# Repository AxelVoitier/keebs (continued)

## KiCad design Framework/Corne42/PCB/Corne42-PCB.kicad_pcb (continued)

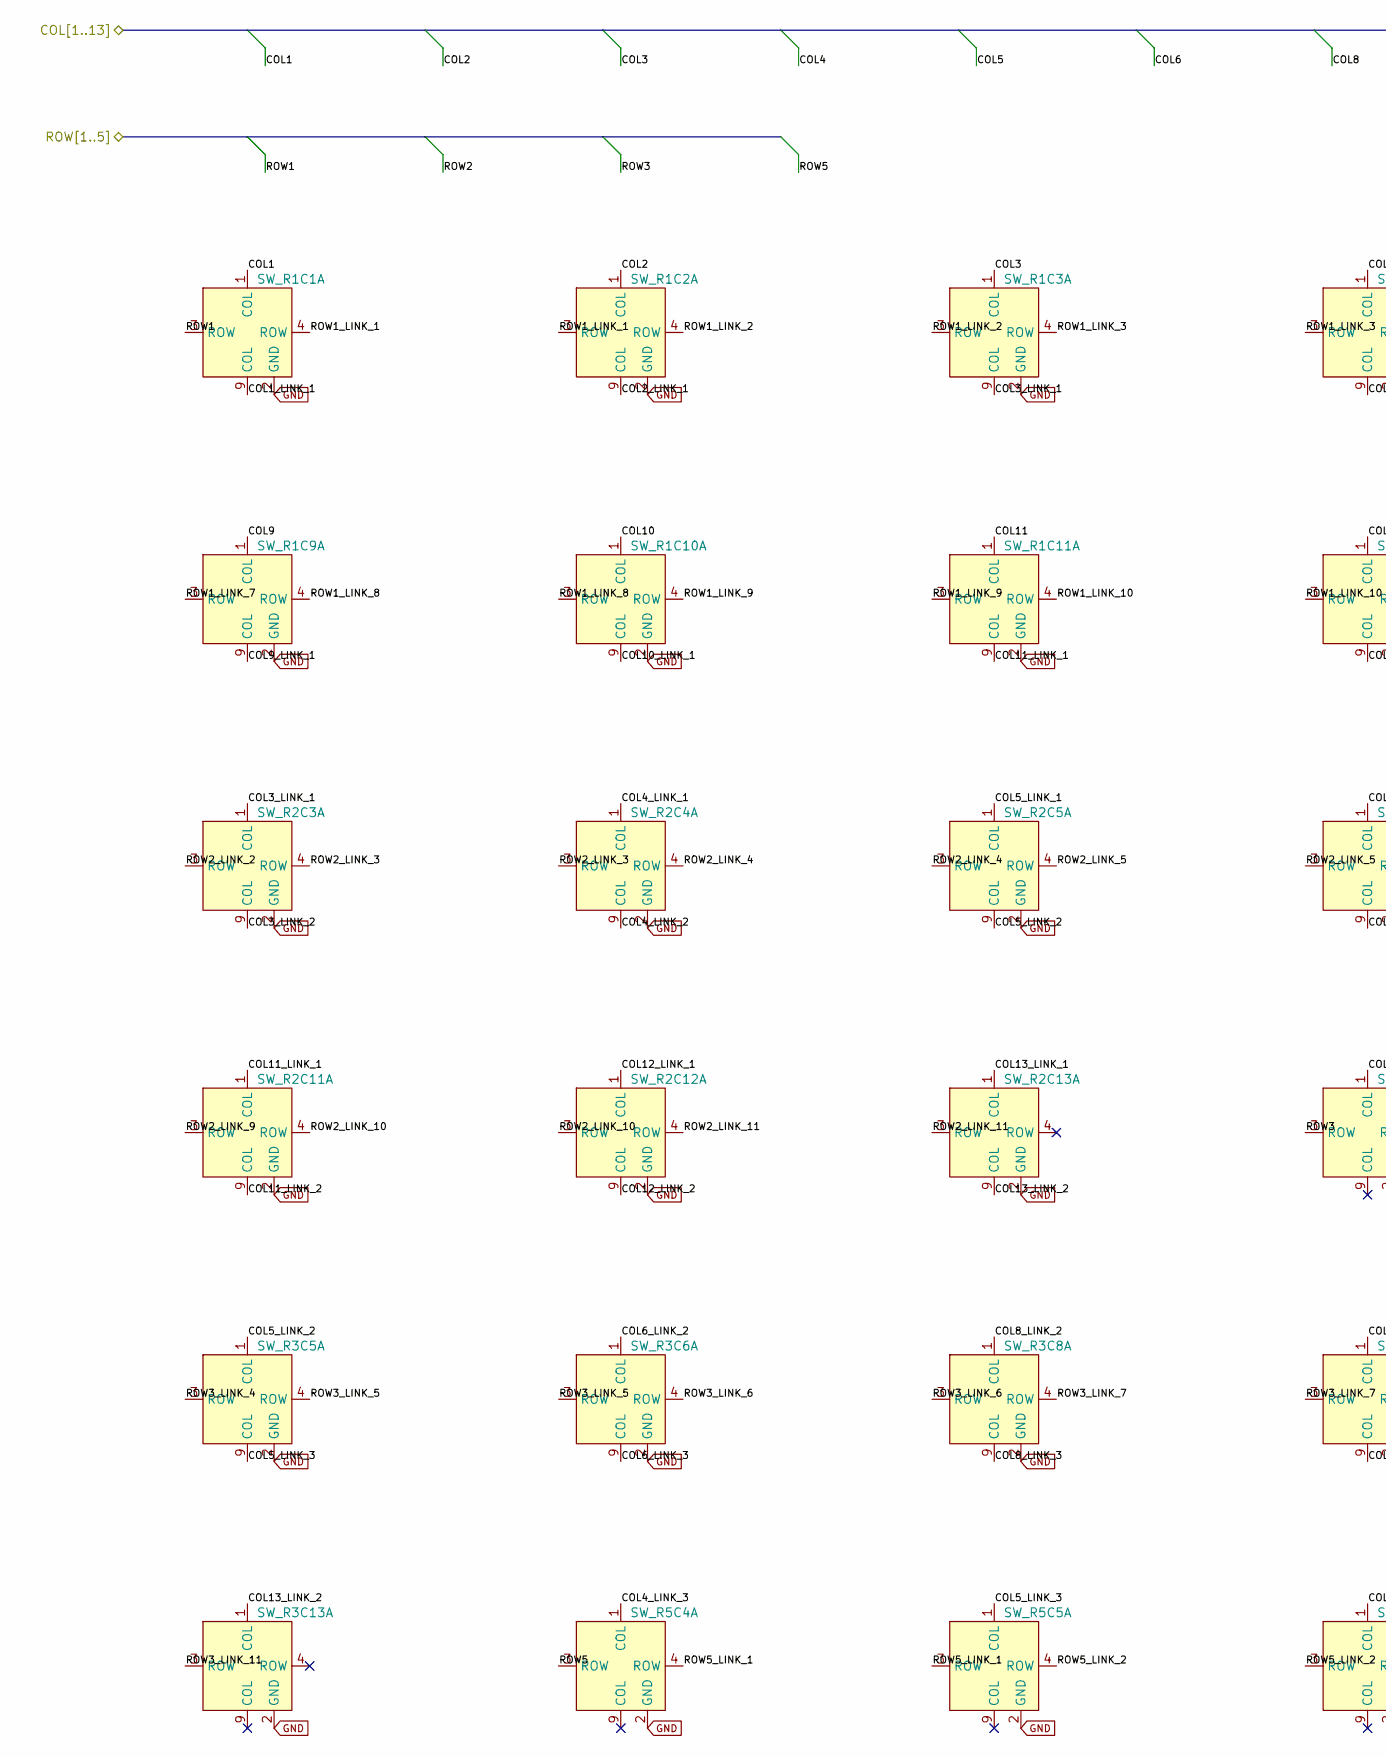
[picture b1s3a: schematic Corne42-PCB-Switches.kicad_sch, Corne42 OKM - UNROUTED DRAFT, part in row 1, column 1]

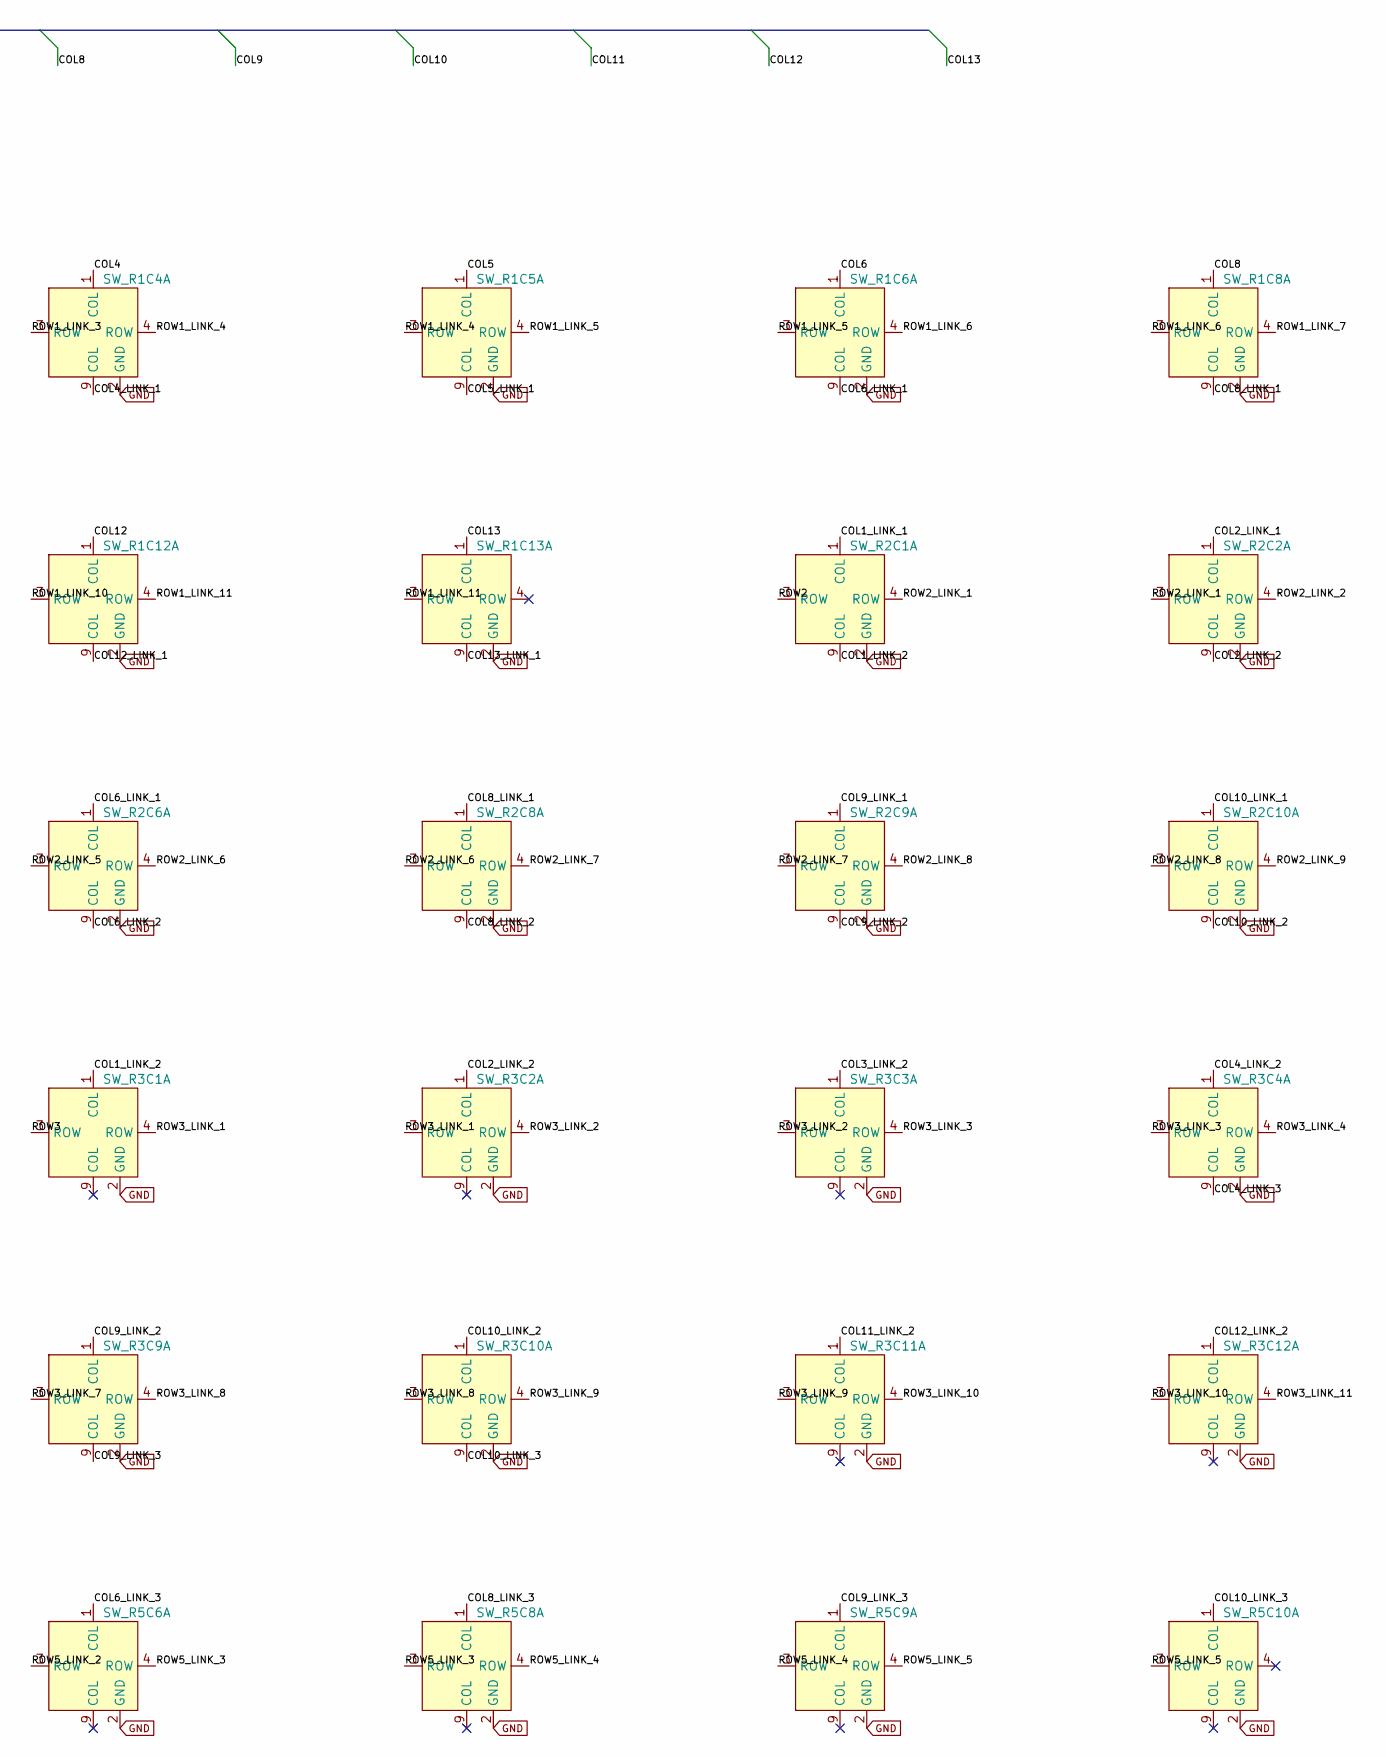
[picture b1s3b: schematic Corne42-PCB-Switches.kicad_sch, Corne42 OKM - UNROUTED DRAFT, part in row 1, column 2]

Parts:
SW_R1C1: One Key Module_Corne42_SW_R1C1
SW_R1C2: One Key Module_Corne42_SW_R1C2
SW_R1C3: One Key Module_Corne42_SW_R1C3
SW_R1C4: One Key Module_Corne42_SW_R1C4
SW_R1C5: One Key Module_Corne42_SW_R1C5
SW_R1C6: One Key Module_Corne42_SW_R1C6
SW_R1C8: One Key Module_Corne42_SW_R1C8
SW_R1C9: One Key Module_Corne42_SW_R1C9
SW_R1C10: One Key Module_Corne42_SW_R1C10
SW_R1C11: One Key Module_Corne42_SW_R1C11
SW_R1C12: One Key Module_Corne42_SW_R1C12
SW_R1C13: One Key Module_Corne42_SW_R1C13
SW_R2C1: One Key Module_Corne42_SW_R2C1
SW_R2C2: One Key Module_Corne42_SW_R2C2
SW_R2C3: One Key Module_Corne42_SW_R2C3
SW_R2C4: One Key Module_Corne42_SW_R2C4
SW_R2C5: One Key Module_Corne42_SW_R2C5
SW_R2C6: One Key Module_Corne42_SW_R2C6
SW_R2C8: One Key Module_Corne42_SW_R2C8
SW_R2C9: One Key Module_Corne42_SW_R2C9
SW_R2C10: One Key Module_Corne42_SW_R2C10
SW_R2C11: One Key Module_Corne42_SW_R2C11
SW_R2C12: One Key Module_Corne42_SW_R2C12
SW_R2C13: One Key Module_Corne42_SW_R2C13
SW_R3C1: One Key Module_Corne42_SW_R3C1
SW_R3C2: One Key Module_Corne42_SW_R3C2
SW_R3C3: One Key Module_Corne42_SW_R3C3
SW_R3C4: One Key Module_Corne42_SW_R3C4
SW_R3C5: One Key Module_Corne42_SW_R3C5
SW_R3C6: One Key Module_Corne42_SW_R3C6
SW_R3C8: One Key Module_Corne42_SW_R3C8
SW_R3C9: One Key Module_Corne42_SW_R3C9
SW_R3C10: One Key Module_Corne42_SW_R3C10
SW_R3C11: One Key Module_Corne42_SW_R3C11
SW_R3C12: One Key Module_Corne42_SW_R3C12
SW_R3C13: One Key Module_Corne42_SW_R3C13
SW_R5C4: One Key Module_Corne42_SW_R5C4
SW_R5C5: One Key Module_Corne42_SW_R5C5
SW_R5C6: One Key Module_Corne42_SW_R5C6
SW_R5C8: One Key Module_Corne42_SW_R5C8
SW_R5C9: One Key Module_Corne42_SW_R5C9
SW_R5C10: One Key Module_Corne42_SW_R5C10

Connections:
/COL1: SW_R1C1.1 (COL); also elsewhere on the board
/COL2: SW_R1C2.1 (COL); also elsewhere on the board
/COL3: SW_R1C3.1 (COL); also elsewhere on the board
/COL4: SW_R1C4.1 (COL); also elsewhere on the board
/COL5: SW_R1C5.1 (COL); also elsewhere on the board
/COL6: SW_R1C6.1 (COL); also elsewhere on the board
/COL8: SW_R1C8.1 (COL); also elsewhere on the board
/COL9: SW_R1C9.1 (COL); also elsewhere on the board
/COL10: SW_R1C10.1 (COL); also elsewhere on the board
/COL11: SW_R1C11.1 (COL); also elsewhere on the board
/COL12: SW_R1C12.1 (COL); also elsewhere on the board
/COL13: SW_R1C13.1 (COL); also elsewhere on the board
/ROW1: SW_R1C1.3 (ROW); also elsewhere on the board
/ROW2: SW_R2C1.3 (ROW); also elsewhere on the board
/ROW3: SW_R3C1.3 (ROW); also elsewhere on the board
/ROW5: SW_R5C4.3 (ROW); also elsewhere on the board
/Switches/COL1_LINK_1: SW_R1C1.9 (COL), SW_R2C1.1 (COL)
/Switches/COL1_LINK_2: SW_R2C1.9 (COL), SW_R3C1.1 (COL)
/Switches/COL2_LINK_1: SW_R1C2.9 (COL), SW_R2C2.1 (COL)
/Switches/COL2_LINK_2: SW_R2C2.9 (COL), SW_R3C2.1 (COL)
/Switches/COL3_LINK_1: SW_R1C3.9 (COL), SW_R2C3.1 (COL)
/Switches/COL3_LINK_2: SW_R2C3.9 (COL), SW_R3C3.1 (COL)
/Switches/COL4_LINK_1: SW_R1C4.9 (COL), SW_R2C4.1 (COL)
/Switches/COL4_LINK_2: SW_R2C4.9 (COL), SW_R3C4.1 (COL)
/Switches/COL4_LINK_3: SW_R3C4.9 (COL), SW_R5C4.1 (COL)
/Switches/COL5_LINK_1: SW_R1C5.9 (COL), SW_R2C5.1 (COL)
/Switches/COL5_LINK_2: SW_R2C5.9 (COL), SW_R3C5.1 (COL)
/Switches/COL5_LINK_3: SW_R3C5.9 (COL), SW_R5C5.1 (COL)
/Switches/COL6_LINK_1: SW_R1C6.9 (COL), SW_R2C6.1 (COL)
/Switches/COL6_LINK_2: SW_R2C6.9 (COL), SW_R3C6.1 (COL)
/Switches/COL6_LINK_3: SW_R3C6.9 (COL), SW_R5C6.1 (COL)
/Switches/COL8_LINK_1: SW_R1C8.9 (COL), SW_R2C8.1 (COL)
/Switches/COL8_LINK_2: SW_R2C8.9 (COL), SW_R3C8.1 (COL)
/Switches/COL8_LINK_3: SW_R3C8.9 (COL), SW_R5C8.1 (COL)
/Switches/COL9_LINK_1: SW_R1C9.9 (COL), SW_R2C9.1 (COL)
/Switches/COL9_LINK_2: SW_R2C9.9 (COL), SW_R3C9.1 (COL)
/Switches/COL9_LINK_3: SW_R3C9.9 (COL), SW_R5C9.1 (COL)
/Switches/COL10_LINK_1: SW_R1C10.9 (COL), SW_R2C10.1 (COL)
/Switches/COL10_LINK_2: SW_R2C10.9 (COL), SW_R3C10.1 (COL)
/Switches/COL10_LINK_3: SW_R3C10.9 (COL), SW_R5C10.1 (COL)
/Switches/COL11_LINK_1: SW_R1C11.9 (COL), SW_R2C11.1 (COL)
/Switches/COL11_LINK_2: SW_R2C11.9 (COL), SW_R3C11.1 (COL)
/Switches/COL12_LINK_1: SW_R1C12.9 (COL), SW_R2C12.1 (COL)
/Switches/COL12_LINK_2: SW_R2C12.9 (COL), SW_R3C12.1 (COL)
/Switches/COL13_LINK_1: SW_R1C13.9 (COL), SW_R2C13.1 (COL)
/Switches/COL13_LINK_2: SW_R2C13.9 (COL), SW_R3C13.1 (COL)
/Switches/ROW1_LINK_1: SW_R1C1.4 (ROW), SW_R1C2.3 (ROW)
/Switches/ROW1_LINK_2: SW_R1C2.4 (ROW), SW_R1C3.3 (ROW)
/Switches/ROW1_LINK_3: SW_R1C3.4 (ROW), SW_R1C4.3 (ROW)
/Switches/ROW1_LINK_4: SW_R1C4.4 (ROW), SW_R1C5.3 (ROW)
/Switches/ROW1_LINK_5: SW_R1C5.4 (ROW), SW_R1C6.3 (ROW)
/Switches/ROW1_LINK_6: SW_R1C6.4 (ROW), SW_R1C8.3 (ROW)
/Switches/ROW1_LINK_7: SW_R1C8.4 (ROW), SW_R1C9.3 (ROW)
/Switches/ROW1_LINK_8: SW_R1C9.4 (ROW), SW_R1C10.3 (ROW)
/Switches/ROW1_LINK_9: SW_R1C10.4 (ROW), SW_R1C11.3 (ROW)
/Switches/ROW1_LINK_10: SW_R1C11.4 (ROW), SW_R1C12.3 (ROW)
/Switches/ROW1_LINK_11: SW_R1C12.4 (ROW), SW_R1C13.3 (ROW)
/Switches/ROW2_LINK_1: SW_R2C1.4 (ROW), SW_R2C2.3 (ROW)
/Switches/ROW2_LINK_2: SW_R2C2.4 (ROW), SW_R2C3.3 (ROW)
/Switches/ROW2_LINK_3: SW_R2C3.4 (ROW), SW_R2C4.3 (ROW)
/Switches/ROW2_LINK_4: SW_R2C4.4 (ROW), SW_R2C5.3 (ROW)
/Switches/ROW2_LINK_5: SW_R2C5.4 (ROW), SW_R2C6.3 (ROW)
/Switches/ROW2_LINK_6: SW_R2C6.4 (ROW), SW_R2C8.3 (ROW)
/Switches/ROW2_LINK_7: SW_R2C8.4 (ROW), SW_R2C9.3 (ROW)
/Switches/ROW2_LINK_8: SW_R2C9.4 (ROW), SW_R2C10.3 (ROW)
/Switches/ROW2_LINK_9: SW_R2C10.4 (ROW), SW_R2C11.3 (ROW)
/Switches/ROW2_LINK_10: SW_R2C11.4 (ROW), SW_R2C12.3 (ROW)
/Switches/ROW2_LINK_11: SW_R2C12.4 (ROW), SW_R2C13.3 (ROW)
/Switches/ROW3_LINK_1: SW_R3C1.4 (ROW), SW_R3C2.3 (ROW)
/Switches/ROW3_LINK_2: SW_R3C2.4 (ROW), SW_R3C3.3 (ROW)
/Switches/ROW3_LINK_3: SW_R3C3.4 (ROW), SW_R3C4.3 (ROW)
/Switches/ROW3_LINK_4: SW_R3C4.4 (ROW), SW_R3C5.3 (ROW)
/Switches/ROW3_LINK_5: SW_R3C5.4 (ROW), SW_R3C6.3 (ROW)
/Switches/ROW3_LINK_6: SW_R3C6.4 (ROW), SW_R3C8.3 (ROW)
/Switches/ROW3_LINK_7: SW_R3C8.4 (ROW), SW_R3C9.3 (ROW)
/Switches/ROW3_LINK_8: SW_R3C9.4 (ROW), SW_R3C10.3 (ROW)
/Switches/ROW3_LINK_9: SW_R3C10.4 (ROW), SW_R3C11.3 (ROW)
/Switches/ROW3_LINK_10: SW_R3C11.4 (ROW), SW_R3C12.3 (ROW)
/Switches/ROW3_LINK_11: SW_R3C12.4 (ROW), SW_R3C13.3 (ROW)
/Switches/ROW5_LINK_1: SW_R5C4.4 (ROW), SW_R5C5.3 (ROW)
/Switches/ROW5_LINK_2: SW_R5C5.4 (ROW), SW_R5C6.3 (ROW)
/Switches/ROW5_LINK_3: SW_R5C6.4 (ROW), SW_R5C8.3 (ROW)
/Switches/ROW5_LINK_4: SW_R5C8.4 (ROW), SW_R5C9.3 (ROW)
/Switches/ROW5_LINK_5: SW_R5C9.4 (ROW), SW_R5C10.3 (ROW)
GND: SW_R1C1.2 (GND), SW_R1C1.10 (GND), SW_R1C2.2 (GND), SW_R1C2.10 (GND), SW_R1C3.2 (GND), SW_R1C3.10 (GND), SW_R1C4.2 (GND), SW_R1C4.10 (GND), SW_R1C5.2 (GND), SW_R1C5.10 (GND), SW_R1C6.2 (GND), SW_R1C6.10 (GND), SW_R1C8.2 (GND), SW_R1C8.10 (GND), SW_R1C9.2 (GND), SW_R1C9.10 (GND), SW_R1C10.2 (GND), SW_R1C10.10 (GND), SW_R1C11.2 (GND), SW_R1C11.10 (GND), SW_R1C12.2 (GND), SW_R1C12.10 (GND), SW_R1C13.2 (GND), SW_R1C13.10 (GND), SW_R2C1.2 (GND), SW_R2C1.10 (GND), SW_R2C2.2 (GND), SW_R2C2.10 (GND), SW_R2C3.2 (GND), SW_R2C3.10 (GND), SW_R2C4.2 (GND), SW_R2C4.10 (GND), SW_R2C5.2 (GND), SW_R2C5.10 (GND), SW_R2C6.2 (GND), SW_R2C6.10 (GND), SW_R2C8.2 (GND), SW_R2C8.10 (GND), SW_R2C9.2 (GND), SW_R2C9.10 (GND), SW_R2C10.2 (GND), SW_R2C10.10 (GND), SW_R2C11.2 (GND), SW_R2C11.10 (GND), SW_R2C12.2 (GND), SW_R2C12.10 (GND), SW_R2C13.2 (GND), SW_R2C13.10 (GND), SW_R3C1.2 (GND), SW_R3C1.10 (GND), SW_R3C2.2 (GND), SW_R3C2.10 (GND), SW_R3C3.2 (GND), SW_R3C3.10 (GND), SW_R3C4.2 (GND), SW_R3C4.10 (GND), SW_R3C5.2 (GND), SW_R3C5.10 (GND), SW_R3C6.2 (GND), SW_R3C6.10 (GND), SW_R3C8.2 (GND), SW_R3C8.10 (GND), SW_R3C9.2 (GND), SW_R3C9.10 (GND), SW_R3C10.2 (GND), SW_R3C10.10 (GND), SW_R3C11.2 (GND), SW_R3C11.10 (GND), SW_R3C12.2 (GND), SW_R3C12.10 (GND), SW_R3C13.2 (GND), SW_R3C13.10 (GND), SW_R5C4.2 (GND), SW_R5C4.10 (GND), SW_R5C5.2 (GND), SW_R5C5.10 (GND), SW_R5C6.2 (GND), SW_R5C6.10 (GND), SW_R5C8.2 (GND), SW_R5C8.10 (GND), SW_R5C9.2 (GND), SW_R5C9.10 (GND), SW_R5C10.2 (GND), SW_R5C10.10 (GND); also elsewhere on the board

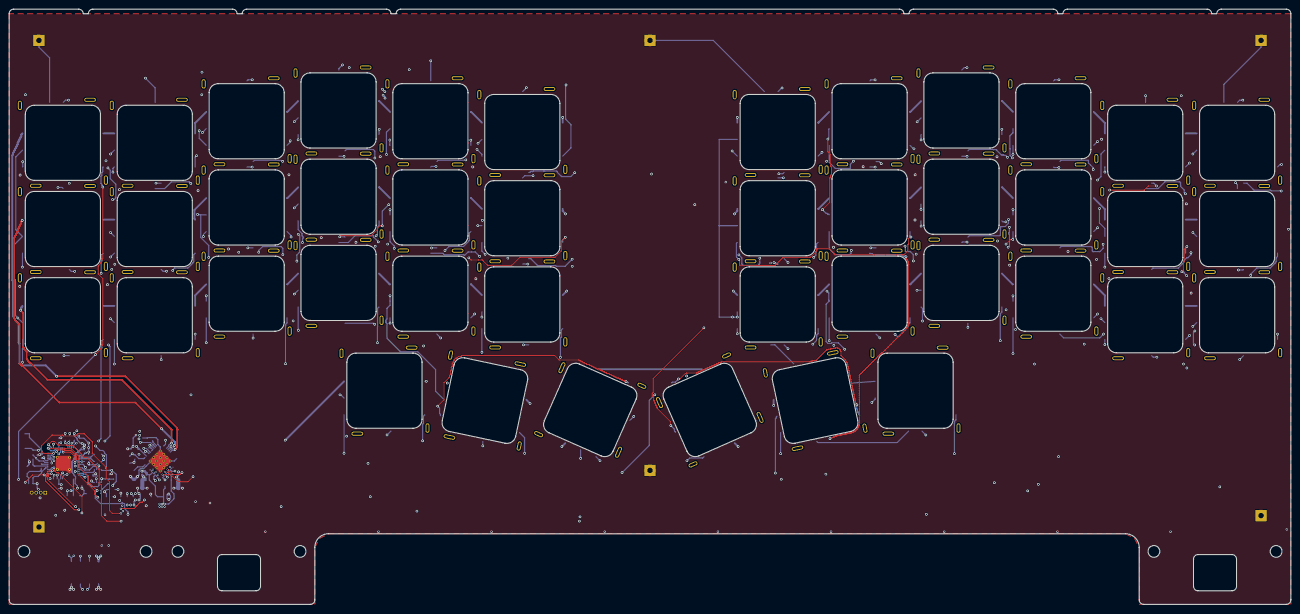
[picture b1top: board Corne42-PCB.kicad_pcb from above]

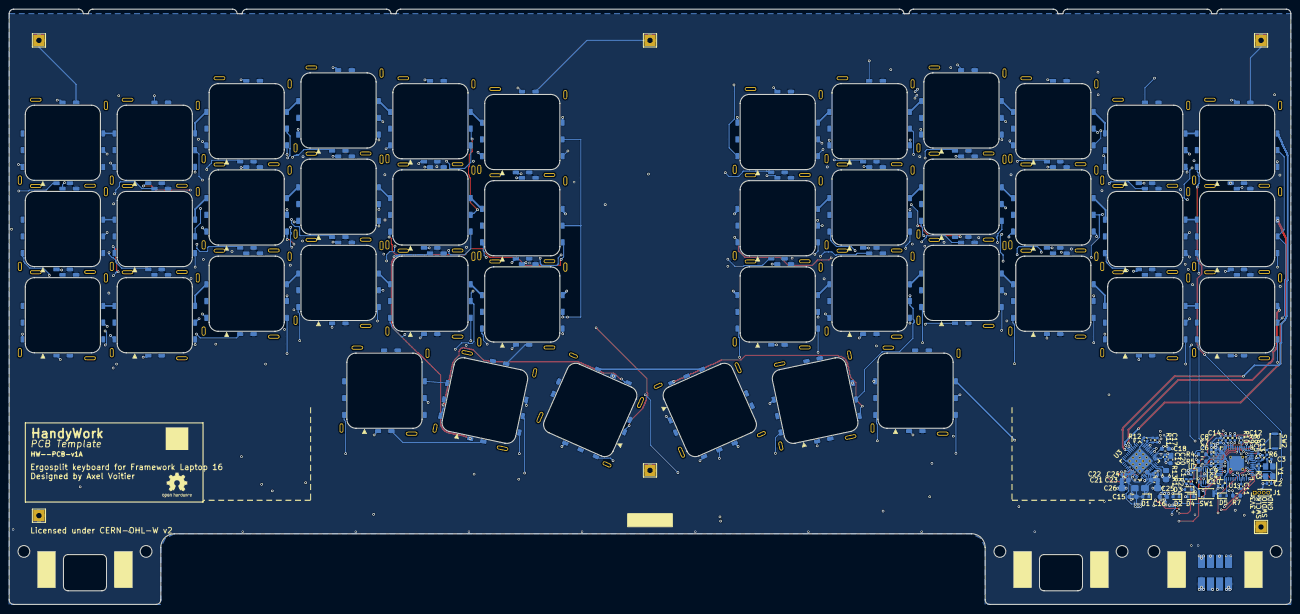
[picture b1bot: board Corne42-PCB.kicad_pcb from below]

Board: 4 copper layers, 283.2 x 131.5 mm, 100 parts (57 on the bottom side), 167 nets.

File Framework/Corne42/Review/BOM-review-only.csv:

"Comment","Designator","Footprint","LCSC Part Number"
"100n","C1,C4,C5,C8,C9,C10,C11,C12,C13,C14,C17,C19,C22,C24","Capacitor_SMD:C_0402_1005Metric","C1525"
"15p","C2,C3","Capacitor_SMD:C_0402_1005Metric","C1548"
"1u","C6,C7","Capacitor_SMD:C_0402_1005Metric","C52923"
"10u","C15,C16","Capacitor_SMD:C_0603_1608Metric","C19702"
"470n","C18,C20,C21,C23","Capacitor_SMD:C_0603_1608Metric","C1623"
"10u","C25,C26","Capacitor_Tantalum_SMD:CP_EIA-3216-18_Kemet-A_HandSolder","C7171"
"TVS","D1,D2,D3,D4,D5","Diode_SMD:D_SOD-523","C20615820"
"1k","R2,R3","Resistor_SMD:R_0402_1005Metric","C11702"
"27.4","R4,R5","Resistor_SMD:R_0603_1608Metric","C25190"
"330k","R7","Resistor_SMD:R_0603_1608Metric","C23137"
"2k","R8,R9","Resistor_SMD:R_0402_1005Metric","C4109"
"100k","R10,R11,R12","Resistor_SMD:R_0402_1005Metric","C25741"
"22k","R13","Resistor_SMD:R_0805_2012Metric_Pad1.20x1.40mm_HandSolder","C17560"
"KXT3","SW1,SW2","Button_Switch_SMD:SW_SPST_CK_KXT3","C221822"
"RP2040","U1","Package_DFN_QFN:QFN-56-1EP_7x7mm_P0.4mm_EP3.2x3.2mm_ThermalVias","C2040"
"W25Q16JV","U2","Package_SON:Winbond_USON-8-1EP_3x2mm_P0.5mm_EP0.2x1.6mm","C2843335"
"IS31FL3733B-QF","U3","Package_DFN_QFN:QFN-48-1EP_6x6mm_P0.4mm_EP4.2x4.2mm_ThermalVias","C5362338"
"12.000 MHz","Y1","Crystal:Crystal_SMD_Abracon_ABM8AIG-4Pin_3.2x2.5mm","C20625731"

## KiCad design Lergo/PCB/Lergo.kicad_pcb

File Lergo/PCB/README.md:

# Lergo modular PCB

## Schematic
[Schematic PDF](Doc/Lergo-schematic.pdf)

## PCB Layout

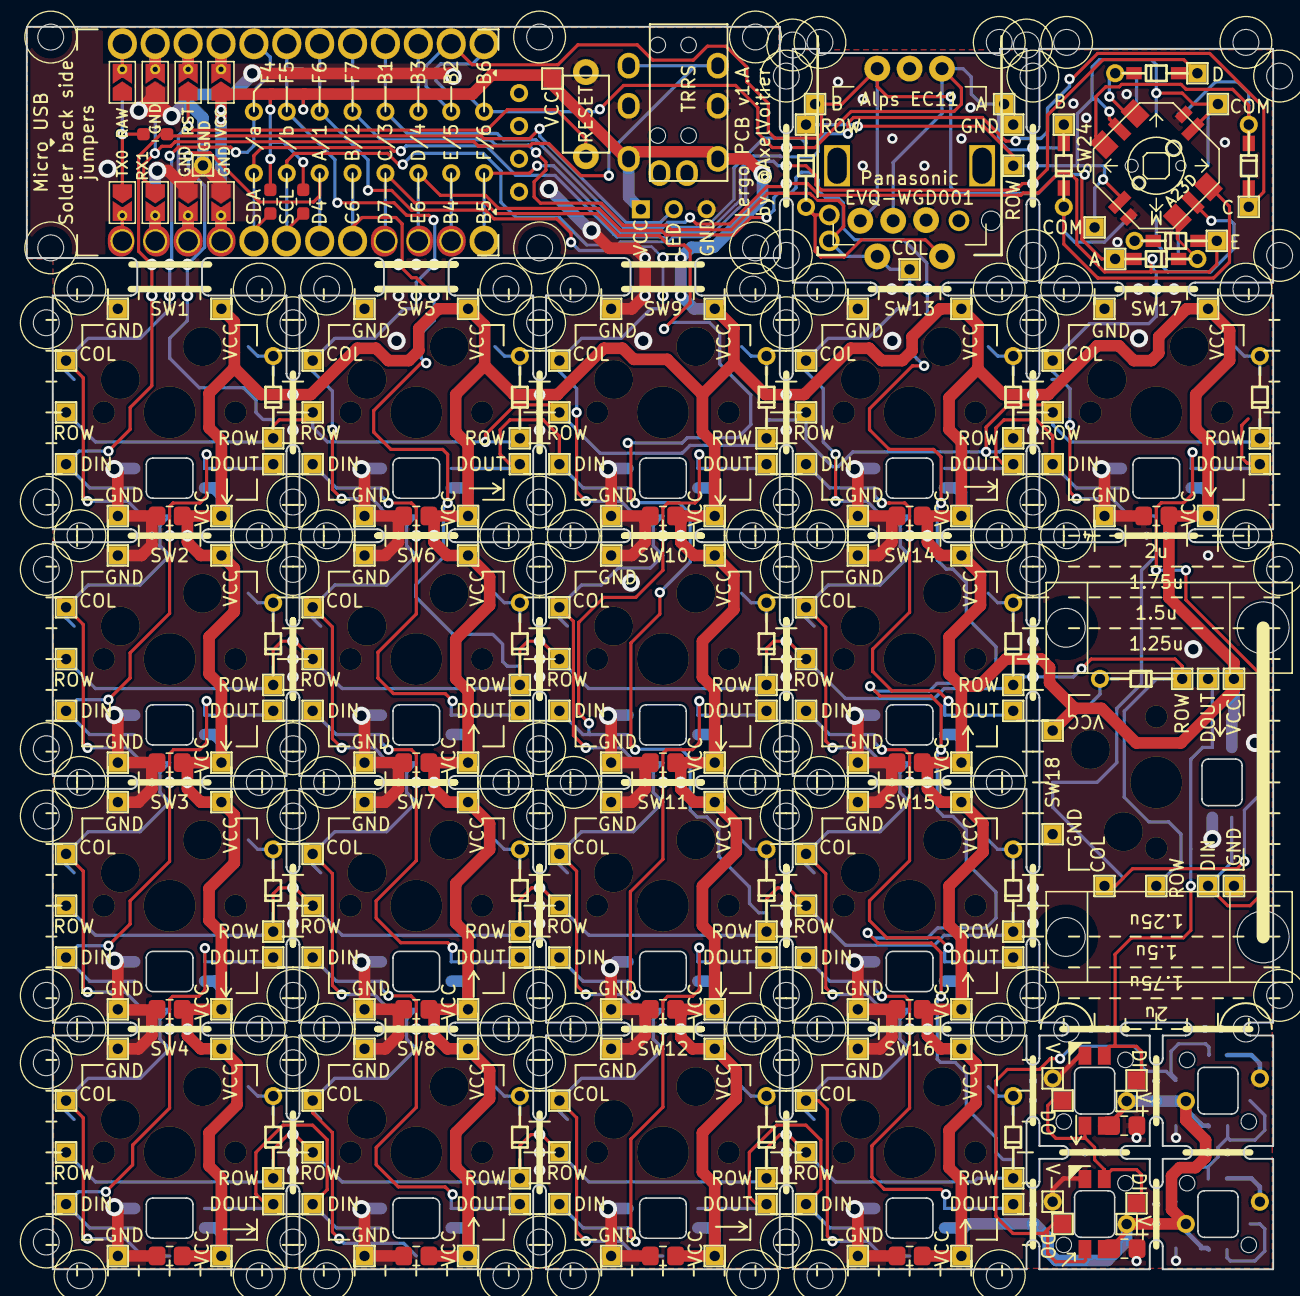
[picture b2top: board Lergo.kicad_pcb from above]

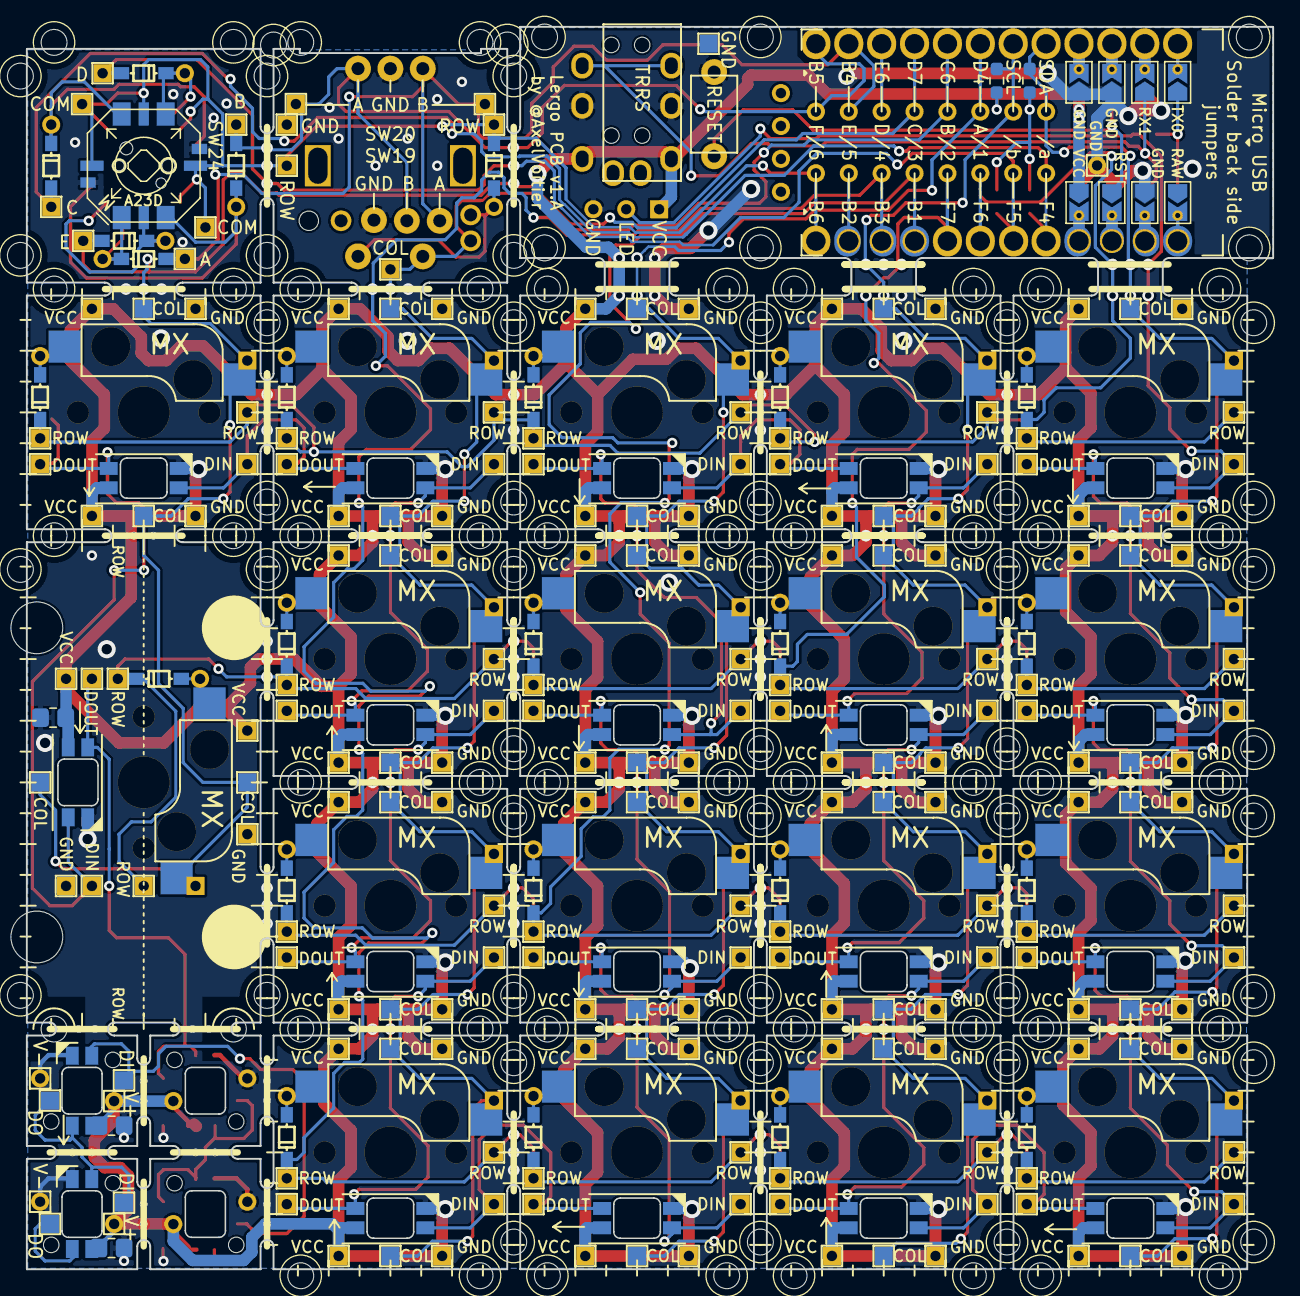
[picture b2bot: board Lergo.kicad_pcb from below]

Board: 2 copper layers, 96.2 x 95.9 mm, 94 parts (26 on the bottom side), 58 nets.

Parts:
%R: SW_Push; CherryMX_Lergo_v1_Module_2_M2
%R#2, %R#3, %R#4, %R#5, %R#6, %R#7, %R#8, %R#9, %R#10: SW_Push; CherryMX_Lergo_v1_Module_2_M2
C19, C20, C21, C22: 100n; C_0603_0805_HandSolder
D1, D2, D3, D4, D5: D_Small; diode_TH_SMD_rev3_alt
D18: D; diode_TH_SMD_rev3
H6, H6#2, H101, H102, H135, H138, H170: MountingHole_Pad; 1pin_rect_conn
H57, H152, H155, H156, H159, H160, H163, H164, H167: MountingHole_Pad; 1pin_conn
H153, H154, H157, H158, H161, H162, H165, H166, H168, H169: MountingHole_Pad; 1pad_conn
J1, J6: MJ-4PP-9
J2: Conn_01x03; PinHeader_1x03_P2.54mm_Vertical
J3, J4: Conn_01x08; PinHeader_1x08_P2.54mm_Vertical_rev2
JP101, JP102, JP103, JP104, JP105, JP106, JP107, JP108: SolderJumper_3_Open; SolderJumper-3_P1.3mm_Open_TrianglePad1.0x1.5mm_duplex
LED1, LED2, LED3, LED4: LED_SK6812_Mini_E; SK6812_Mini_E
R101: 510R; R_0603_1608Metric_Pad0.98x0.95mm_HandSolder
R102, R103, R104, R105: 4k7; R_0603_1608Metric_Pad0.98x0.95mm_HandSolder
Ref**: Val**; M2_Hole_Standoff_Large_Cleareance
Ref**#2: Val**; M2_Hole_Standoff_Large_Cleareance
SW1, SW2, SW3, SW4, SW5, SW6, SW7, SW8, SW9, SW10, SW11, SW12, SW13, SW14, SW15, SW16, SW17: SW_PUSH_LED; CherryMX_Lergo_v1_Module_1u
SW18: SW_PUSH_LED; CherryMX_Lergo_v1_Module_2u
SW19: Rotary_Encoder_Switch; RollerEncoder_Panasonic_EVQWGD001_No_Cutout
SW20: Rotary_Encoder_Switch; RotaryEncoder_Alps_EC11E-Switch_Vertical_H20mm_rev2
SW22: SW_Push; ResetSW
SW24, SW24#2: 5way_switch; Five_Way_Switch_Panasonic_EVQQ7
U1: ProMicro; Arduino_ProMicro_Rivets

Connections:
GND: C19.1, C20.1, C21.1, C22.1, H57.1, H155.1, H159.1, H163.1, H167.1, H169.1, H170.1, J1.C, J2.3, J6.C, JP101.1, JP102.1, JP103.3, JP106.1, JP107.3, JP108.3, LED1.3, LED2.3, LED3.3, LED4.3, SW1.3, SW2.3, SW3.3, SW4.3, SW5.3, SW6.3, SW7.3, SW8.3, SW9.3, SW10.3, SW11.3, SW12.3, SW13.3, SW14.3, SW15.3, SW16.3, SW17.3, SW18.3, SW19.C, SW20.C, SW22.2, SW24.GND, SW24#2.GND
unnamed: D1.1, SW24.A, SW24#2.A
unnamed: D2.1, SW24.E, SW24#2.E
unnamed: D3.1, SW24.B, SW24#2.B
unnamed: D4.1, SW24.C, SW24#2.C
unnamed: D5.1, SW24.D, SW24#2.D
unnamed: D18.2, SW19.S2, SW20.S2
unnamed: H153.1, H158.1, LED1.2, LED2.4
unnamed: H154.1, LED1.4, SW18.2
unnamed: H157.1, H162.1, LED2.2, LED3.4
unnamed: H161.1, H166.1, LED3.2, LED4.4
unnamed: H165.1, LED4.2
unnamed: JP101.2, U1.4
unnamed: JP102.2, U1.3
unnamed: JP103.2, U1.2
unnamed: JP104.2, U1.1
unnamed: JP105.2, U1.24
unnamed: JP106.2, U1.23
unnamed: JP107.2, U1.22
unnamed: JP108.2, U1.21
unnamed: SW1.2, SW2.4
unnamed: SW2.2, SW3.4
unnamed: SW3.2, SW4.4
unnamed: SW4.2, SW8.4
unnamed: SW5.2, SW9.4
unnamed: SW5.4, SW6.2
unnamed: SW6.4, SW7.2
unnamed: SW7.4, SW8.2
unnamed: SW10.2, SW11.4
unnamed: SW9.2, SW10.4
unnamed: SW11.2, SW12.4
unnamed: SW12.2, SW16.4
unnamed: SW13.2, SW17.4
unnamed: SW13.4, SW14.2
unnamed: SW14.4, SW15.2
unnamed: SW15.4, SW16.2
unnamed: SW17.2, SW18.4
VCC: C19.2, C20.2, C21.2, C22.2, H152.1, H156.1, H160.1, H164.1, H168.1, J1.D, J2.1, J6.D, JP101.3, JP108.1, LED1.1, LED2.1, LED3.1, LED4.1, R102.2, R103.2, R104.2, R105.2, SW1.1, SW2.1, SW3.1, SW4.1, SW5.1, SW6.1, SW7.1, SW8.1, SW9.1, SW10.1, SW11.1, SW12.1, SW13.1, SW14.1, SW15.1, SW16.1, SW17.1, SW18.1
X1: J4.1, R102.1, SW1.5, SW2.5, SW3.5, SW4.5, U1.5
X2: J4.2, R103.1, SW5.5, SW6.5, SW7.5, SW8.5, U1.6
X3: J4.3, SW9.5, SW10.5, SW11.5, SW12.5, U1.7
X4: H135.1, J4.4, SW13.5, SW14.5, SW15.5, SW16.5, SW19.S1, SW20.S1, U1.8
X5: D2.2, J4.5, SW17.5, SW18.5, U1.9
X6: J4.6, U1.10
X7: D1.2, H102.1, J4.7, SW19.A, SW20.B, U1.11
X8: D3.2, H101.1, J4.8, SW19.B, SW20.A, U1.12
X9: D4.2, J3.1, R104.1, U1.20
X10: D5.2, J3.2, R105.1, U1.19
Y1: J3.3, SW1.7, SW5.7, SW9.7, SW13.7, SW17.7, U1.18
Y2: J3.4, SW2.7, SW6.7, SW10.7, SW14.7, SW18.7, U1.17
Y3: J3.5, SW3.7, SW7.7, SW11.7, SW15.7, U1.16
Y4: J3.6, SW4.7, SW8.7, SW12.7, SW16.7, U1.15
Y5: J3.7, U1.14
Y6: D18.1, H6.1, H6#2.1, H138.1, J3.8, SW24.Com, SW24#2.Com, U1.13
data: J1.B, J6.B, JP103.1, JP106.3
led: J2.2, R101.1, SW1.4
led_: JP104.1, JP105.3, R101.2
reset1: JP102.3, JP107.1, SW22.1
